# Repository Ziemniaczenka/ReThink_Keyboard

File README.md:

### Adapting older ThinkPad laptop keyboard modules into standalone keyboards using Framework Control Board.

## Hardware overview
- **Framework Control Board** - nRF54LM20A, Bluetooth/dongle/USB-C connection, nPM1300 power management IC.
- **ReThink Adapter Board** - bridge between Control Board and ThinkPad keyboards.
- **3D Printed case** - housing for components, different for each keyboard type.
- **ThinkPad keyboard modules** - 6 and 7row, classic and chiclet, with or without backlight, with integrated Pointing Stick (nub) and mouse keys. Full list TBD.
- **ZMK Firmware** - based on Zephyr RTOS, provides customizability. Each keyboard type will be different shield. See [rethink-zmk-config](https://github.com/Ziemniaczenka/rethink-zmk-config).

> Note: This is preliminary information. Everything is subject to change and more information will follow.

> [!IMPORTANT]
> While most of this repository is human-written, some of the text was written by AI, mostly in [Adapter bring-up](docs/adapter_bringup.md) and [Adapter v1.0 notes](docs/adapter_notes.md). Do with that information as you will.

## Status

- [x] Adapter Board:    V1.0 designed, parts arrived, first board assembled.
- [ ] Firmware:         repo configured, test configurations WIP.
- [ ] Case:             WIP for T420/T430, not yet started for others.

## Reference pinouts

- [Framework Control Board FFC connectors](docs/pinouts/framework_ffc.md)
- [Mezzanine Connector (e.g. T60/T420)](docs/pinouts/mezzanine.md)
- [FFC1 (e.g. L420)](docs/pinouts/ffc1.md)
- [FFC2 (e.g. T480/T580/L14)](docs/pinouts/ffc2.md)
- [PCAL6416A IO expander](docs/pinouts/io_expander.md) - expander pins, solder jumpers

## Mechanical CAD

- TBD

First case prototype (T420), 3D printed:

##  

Adapter board connects to Control Board using FFC cables, has connectors for different generations of ThinkPad keyboards, boost converters (for pointing stick, backlight) and I2C IO expander (required to keep all keyboard buttons and diodes functional).

Variants:
| Variant        | Connectors       | Backlight |
| -------------- | ---------------- | :-------: |
| Full (Default) | Mezz, FFC1, FFC2 |     ✅     |
| Mezz_no_BL     | Mezz             |     ❌     |
| FFC1           | FFC1             |     ❌     |
| FFC2           | FFC2             |     ✅     |

Solder jumpers change the defaults if needed:
- Pointing Stick supply 5V or 3V3, separately for Mezzanine/FFC1 and FFC2 (with level shifter bypass).
- IO expander supply: always on LED_3V3 (default) or switched TP_3V3.
- Charge pump and backlight boost always on, instead of controlled by the IO expander.
- 5V for T430 backlight on the Mezzanine connector (JP3, **only** for T430-like keyboards).

Defaults, jumper positions and the matching firmware options are in [IO expander](docs/pinouts/io_expander.md).

- [Schematic](circuit/ReThink_adapter_Schematic.pdf)
- [PCB](circuit/ReThink_adapter_PCB.pdf)
- [BOM](circuit/ReThink_adapter/bom/ReThink_adapter_default.csv)
- [Adapter bring-up](docs/adapter_bringup.md).
- [Adapter v1.0 notes](docs/adapter_notes.md): measurements, troubleshooting, next revision.

## Battery

- Picoblade 3-pin with NTC thermistor.
- TBD

## Firmware and Bootloader

- ZMK configuration: [rethink-zmk-config](https://github.com/Ziemniaczenka/rethink-zmk-config) (MIT), work in progress.
- Builds in Docker, the same way locally and on GitHub Actions. No Zephyr SDK needed on the PC.
- Control Board comes with MCUboot, so no programmer is needed. Flashing over USB:
  - hold the pairing button while plugging in USB,
  - or, with battery connected, hold the pairing button for 10s.
- Adapter jumpers and Control Board options (e.g. backlight power source) are set in one file: `config/rethink.conf`.

## Compatibility Table

Planned, nothing tested on real keyboards yet.

| Keyboards                                                                                               | Connector | Backlight <br> (optional) | Pointing Stick supply <br> (**default**) | Board support | Firmware config | Case |
| ------------------------------------------------------------------------------------------------------- | --------- | ------------------------- | ---------------------------------------- | ------------- | --------------- | ---- |
| T60, T61, T400, R60, R61, R400, R500, W500, W700                                                        | Mezzanine | ❌                         | 5V                                       |               |                 |      |
| T410, T420, T510, T520, W510, W520, X220                                                                | Mezzanine | ❌                         | 5V                                       | ✅             | WIP             | WIP  |
| T430, T530, W530, X230                                                                                  | Mezzanine | ✅                         | 5V                                       |               |                 |      |
| L410, L412, L420, L421, L510, L512,<br>L520, SL300, SL410, SL510                                        | FFC1      | ❌                         | 5V                                       | ✅             | WIP             |      |
| T470, T480, A475, A485                                                                                  | FFC2      | ✅                         | 3V3                                      |               |                 |      |
| T570, T580, P51s, P52s                                                                                  | FFC2      | ✅                         | 3V3                                      |               |                 |      |
| L14g1, L14g2                                                                                            | FFC2      | ✅                         | 3V3                                      |               |                 |      |
| L15g1, L15g2                                                                                            | FFC2      | ✅                         | 3V3                                      |               |                 |      |
| E480, E485, E490, E495, L380, L390, L480, L490, T480s,<br>T490, T14g1, T14g2, P43, P43s, P14sG1, P14sG2 | FFC2      | ✅                         | 3V3                                      |               |                 |      |
| E580, E585, E590, E595, L580, L590,<br>T590, P52, P53, P53s, P72, P73                                   | FFC2      | ✅                         | 3V3                                      |               |                 |      |
| T15g1, T15g2, P15sG1, P15sG2                                                                            | FFC2      | ✅                         | 3V3                                      |               |                 |      |
| P15g1, P15g2, P17g1, P17g2                                                                              | FFC2      | ✅                         | 3V3                                      |               |                 |      |

Full lists in the connector pinouts.

## License

ReThink keyboard by Ziemniaczenka is licensed under CC BY-SA 4.0.
To view a copy of this license, visit https://creativecommons.org/licenses/by-sa/4.0/

Firmware ([rethink-zmk-config](https://github.com/Ziemniaczenka/rethink-zmk-config)) is licensed under MIT.

Component 3D models located under `circuit/libraries/3dmodels/` are the intellectual property of their respective manufacturers and are provided for reference/visualization purposes only. They are not covered by the above license; all rights remain with their original owners.

## Disclaimers
> Framework Control Board was provided pre-release by Framework Computer Inc. through Control Board Developer Program.

> ThinkPad and TrackPoint are registered trademarks of Lenovo. ReThink is an independent open-source project and is not affiliated with, endorsed by, or certified by Lenovo Group Limited.

## References
1. https://github.com/FrameworkComputer/Framework-Wireless-Touchpad-Keyboard
2. https://github.com/badjeff/kb_zmk_ps2_mouse_trackpoint_driver
3. https://github.com/rampadc/zmk-thinkpad
4. https://github.com/delingren/thinkpad_keyboards
5. https://github.com/Shaedil/zmk-config-fw-cb
6. https://github.com/zmkfirmware/zmk/pull/3387

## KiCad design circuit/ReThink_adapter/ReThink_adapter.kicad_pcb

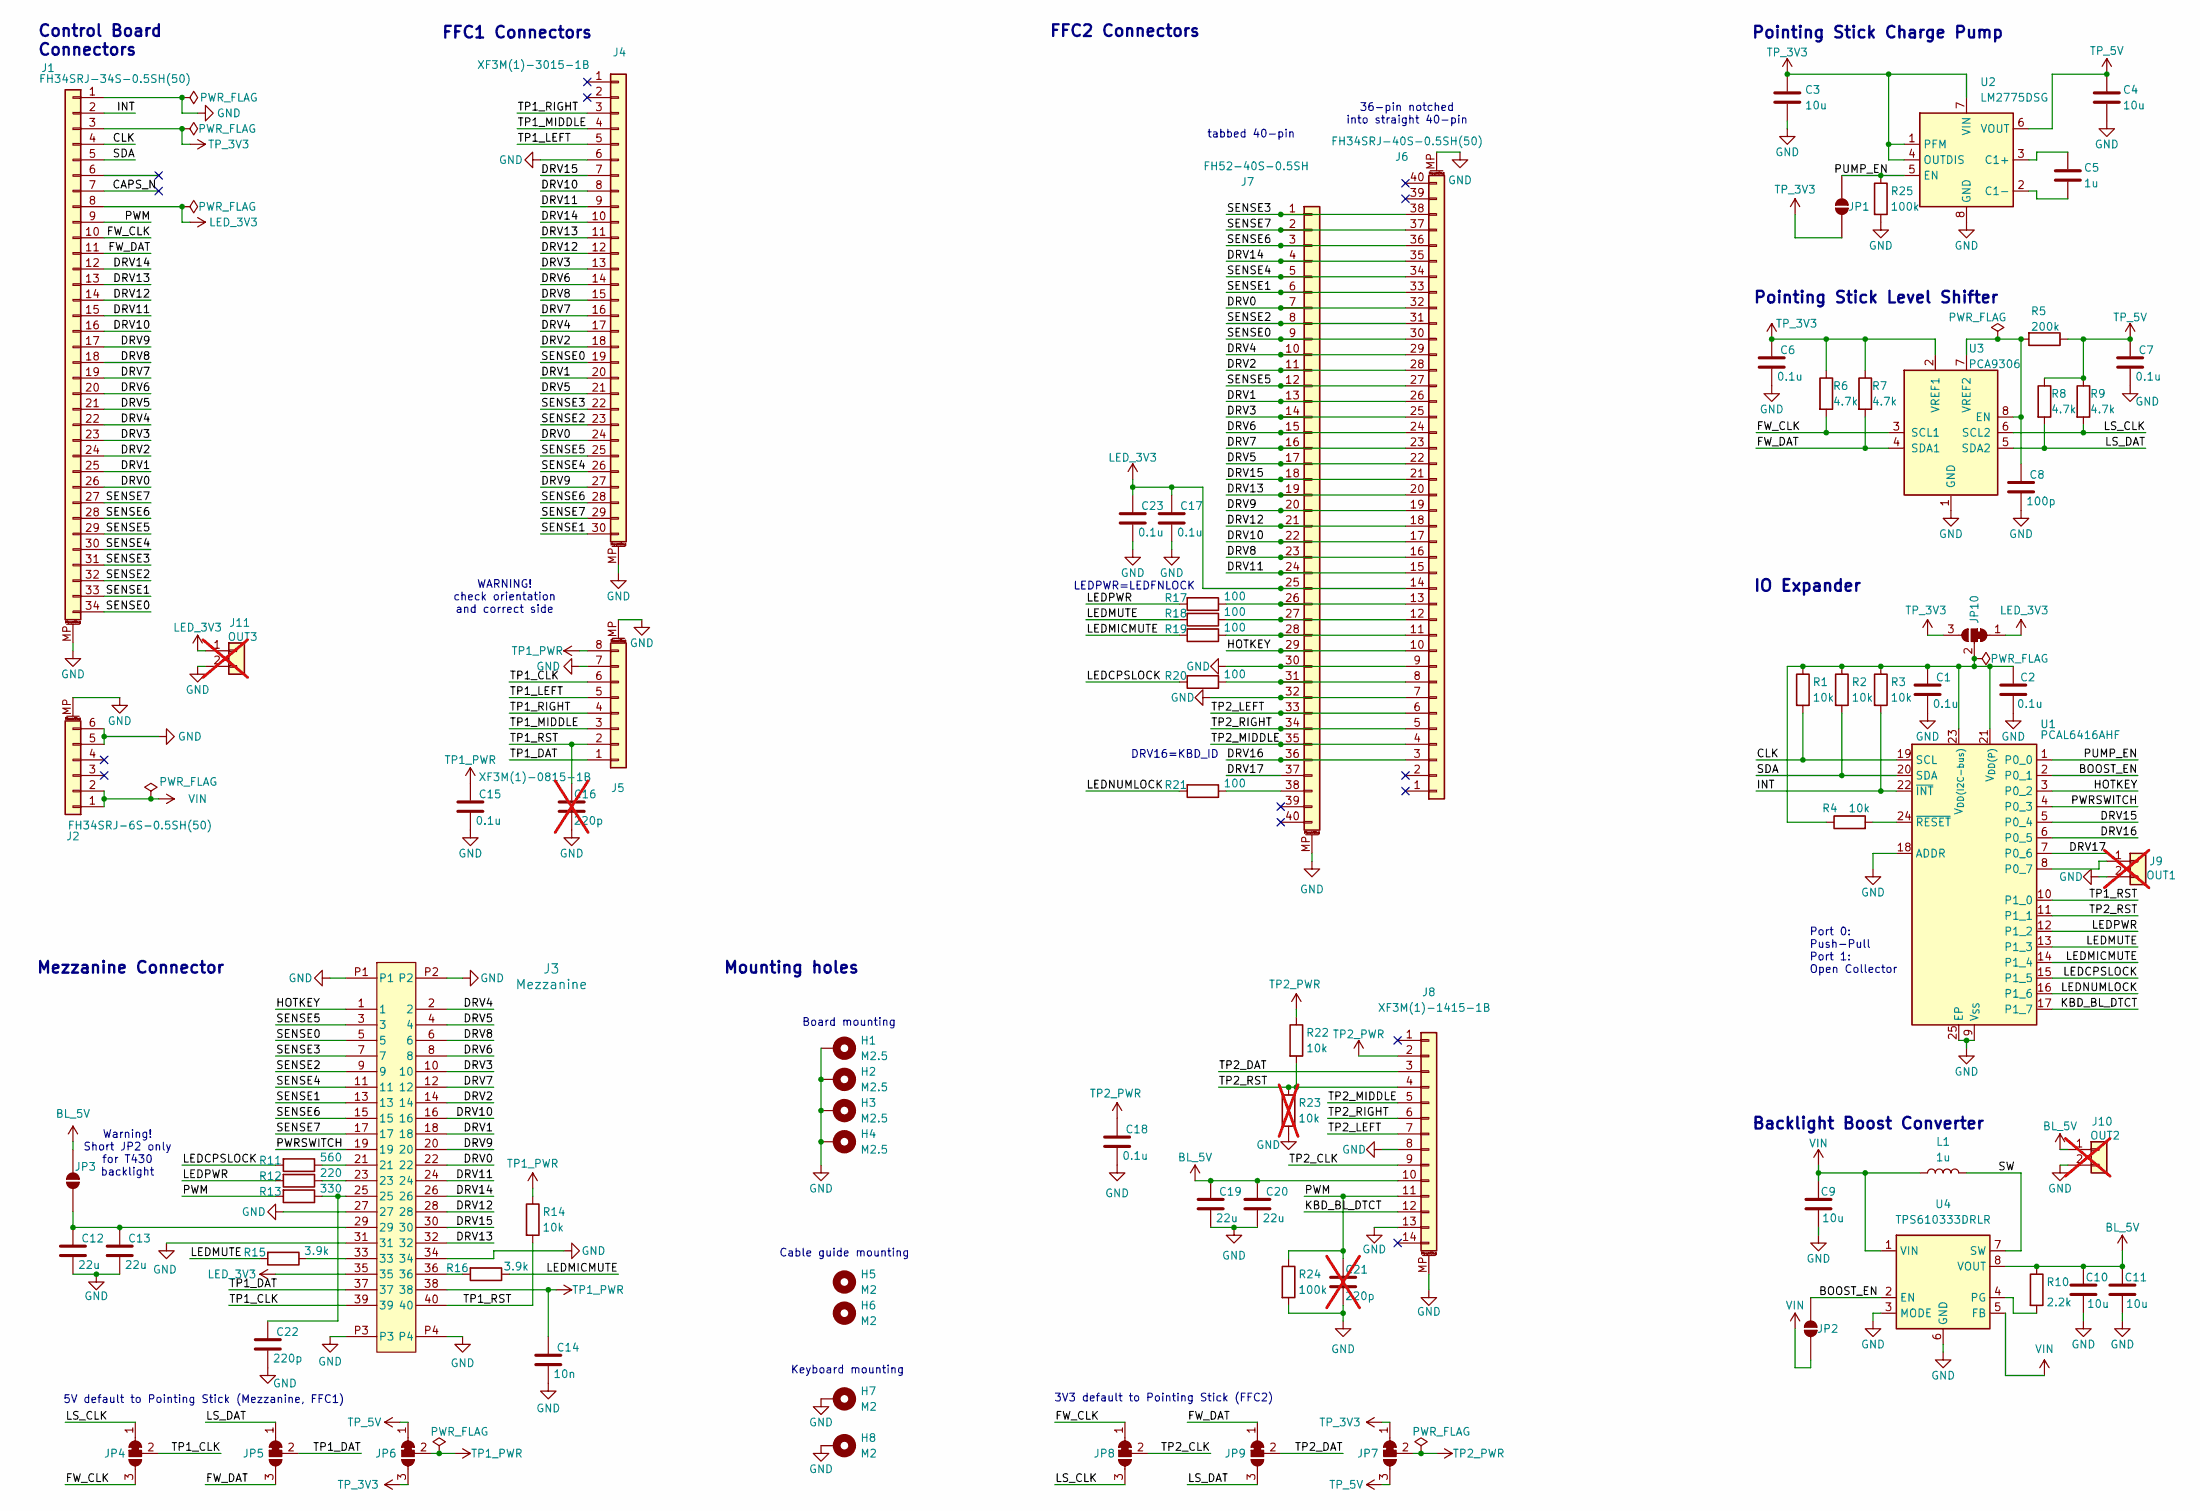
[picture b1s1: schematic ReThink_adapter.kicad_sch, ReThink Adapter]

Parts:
C1, C2, C6, C7, C15, C17, C18, C23: 0.1u; C_0402_1005Metric; Voltage 16; MPN GRM155R71H104KE14D; DigiKey_PN 490-10700-1-ND
C3, C4, C9, C10, C11: 10u; C_0603_1608Metric; Voltage 16; MPN GRM188R61E106MA73J; DigiKey_PN 1276-1869-1-ND
C5: 1u; C_0603_1608Metric; Voltage 10; MPN MLAST168SB7105KTNA01; DigiKey_PN 587-MLAST168SB7105KTNA01CT-ND
C8: 100p; C_0402_1005Metric; Voltage 25; MPN GRM1555C2A101GA01D; DigiKey_PN 490-GRM1555C2A101GA01DCT-ND
C12, C13, C19, C20: 22u; C_0805_2012Metric; Voltage 16; MPN GRM219R61C226ME15K; DigiKey_PN 490-GRM219R61C226ME15KCT-ND
C14: 10n; C_0402_1005Metric; Voltage 25; MPN CL05B103KB5NNNC; DigiKey_PN 1276-1028-1-ND
C16, C21: 220p; C_0402_1005Metric; Voltage 25; MPN C0402C221J2GACTU; DigiKey_PN 399-C0402C221J2GACTUCT-ND; not fitted
C22: 220p; C_0402_1005Metric; Voltage 25; MPN C0402C221J2GACTU; DigiKey_PN 399-C0402C221J2GACTUCT-ND
H1, H2, H3, H4: M2.5; MountingHole_2.7mm_M2.5_DIN965_Pad
H5, H6: M2; MountingHole_2.2mm_M2_ISO14580
H7, H8: M2; MountingHole_2.2mm_M2_ISO14580_Pad
J1: FH34SRJ-34S-0.5SH(50); MPN FH34SRJ-34S-0.5SH(50); DigiKey_PN 26-FH34SRJ-34S-0.5SH(50)CT-ND
J2: FH34SRJ-6S-0.5SH(50); MPN FH34SRJ-6S-0.5SH(50); DigiKey_PN H125773CT-ND
J3: Mezzanine; Mezzanine_combo; MPN AA01B-S040VA1; DigiKey_PN WM6787CT-ND
J4: XF3M(1)-3015-1B; MPN XF3M(1)-3015-1B; DigiKey_PN OR1179CT-ND
J5: XF3M(1)-0815-1B; MPN XF3M(1)-0815-1B; DigiKey_PN OR1222CT-ND
J6: FH34SRJ-40S-0.5SH(50); MPN FH34SRJ-40S-0.5SH(50); DigiKey_PN H125755CT-ND
J7: FH52-40S-0.5SH; MPN FH52-40S-0.5SH; DigiKey_PN HFZ040CT-ND
J8: XF3M(1)-1415-1B; MPN XF3M(1)-1415-1B; DigiKey_PN Z5875CT-ND
J9: OUT1; PinHeader_1x02_P2.54mm_Vertical; not fitted
J10: OUT2; PinHeader_1x02_P2.54mm_Vertical; not fitted
J11: OUT3; PinHeader_1x02_P2.54mm_Vertical; not fitted
JP1, JP2, JP3: SolderJumper_2_Open; SolderJumper-2_P1.3mm_Open_RoundedPad1.0x1.5mm
JP4, JP5, JP6, JP7, JP8, JP9, JP10: SolderJumper_3_Bridged12; SolderJumper-3_P1.3mm_Bridged12_RoundedPad1.0x1.5mm_NumberL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
L1: 1u; L_0806_2016Metric; MPN IHHP0806ZHER1R0M01; DigiKey_PN 541-IHHP0806ZHER1R0M01CT-ND
R1, R2, R3, R4, R14, R22: 10k; R_0402_1005Metric; MPN RC0402FR-0710KP; DigiKey_PN YAG1249CT-ND
R5: 200k; R_0402_1005Metric; MPN RC0402FR-07200KP; DigiKey_PN 13-RC0402FR-07200KPCT-ND
R6, R7, R8, R9: 4.7k; R_0402_1005Metric; MPN RC0402FR-074K7P; DigiKey_PN YAG1272CT-ND
R10: 2.2k; R_0402_1005Metric; MPN RC0402FR-072K2P; DigiKey_PN YAG1260CT-ND
R11: 560; R_0402_1005Metric; MPN RC0402FR-07560RL; DigiKey_PN 311-560LRCT-ND
R12: 220; R_0402_1005Metric; MPN RC0402FR-07220RP; DigiKey_PN 13-RC0402FR-07220RPCT-ND
R13: 330; R_0402_1005Metric; MPN RC0402FR-07330RL; DigiKey_PN 311-330LRCT-ND
R15, R16: 3.9k; R_0402_1005Metric; MPN RC0402FR-073K9L; DigiKey_PN 311-3.90KLRCT-ND
R17, R18, R19, R20, R21: 100; R_0402_1005Metric; MPN RC0402FR-07100RP; DigiKey_PN YAG1248CT-ND
R23: 10k; R_0402_1005Metric; MPN RC0402FR-0710KP; DigiKey_PN YAG1249CT-ND; not fitted
R24, R25: 100k; R_0402_1005Metric; MPN RC0402FR-07100KP; DigiKey_PN 13-RC0402FR-07100KPCT-ND
U1: PCAL6416AHF; HVQFN-24-1EP_4x4mm_P0.5mm_EP2.1x2.1mm; MPN PCAL6416AHF,128; DigiKey_PN 568-9946-1-ND
U2: LM2775DSG; Texas_DSG0008A_WSON-8-1EP_2x2mm_P0.5mm_EP0.9x1.6mm; MPN LM2775DSGT; DigiKey_PN 296-42149-1-ND
U3: PCA9306; VSSOP-8_2.3x2mm_P0.5mm; MPN PCA9306DCUR; DigiKey_PN 296-17988-1-ND
U4: TPS610333DRLR; SOT-583-8; MPN TPS610333DRLR; DigiKey_PN 296-TPS610333DRLRCT-ND

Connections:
/BOOST_EN: JP2.2 (B), U1.2 (P0_1), U4.2 (EN)
/CAPS_N: J1.7
/CLK: J1.4, R1.2, U1.19 (SCL)
/DRV0: J1.26, J3.22, J4.24, J6.32, J7.7
/DRV1: J1.25, J3.18, J4.20, J6.26, J7.13
/DRV2: J1.24, J3.14, J4.18, J6.28, J7.11
/DRV3: J1.23, J3.10, J4.13, J6.25, J7.14
/DRV4: J1.22, J3.2, J4.17, J6.29, J7.10
/DRV5: J1.21, J3.4, J4.21, J6.22, J7.17
/DRV6: J1.20, J3.8, J4.14, J6.24, J7.15
/DRV7: J1.19, J3.12, J4.16, J6.23, J7.16
/DRV8: J1.18, J3.6, J4.15, J6.16, J7.23
/DRV9: J1.17, J3.20, J4.27, J6.19, J7.20
/DRV10: J1.16, J3.16, J4.8, J6.17, J7.22
/DRV11: J1.15, J3.24, J4.9, J6.15, J7.24
/DRV12: J1.14, J3.28, J4.12, J6.18, J7.21
/DRV13: J1.13, J3.32, J4.11, J6.20, J7.19
/DRV14: J1.12, J3.26, J4.10, J6.35, J7.4
/DRV15: J3.30, J4.7, J6.21, J7.18, U1.5 (P0_4)
/DRV16: J6.3, J7.36, U1.6 (P0_5)
/DRV17: J7.37, U1.7 (P0_6)
/FW_CLK: J1.10, JP4.3 (B), JP8.1 (A), R6.2, U3.3 (SCL1)
/FW_DAT: J1.11, JP5.3 (B), JP9.1 (A), R7.2, U3.4 (SDA1)
/HOTKEY: J3.1, J6.10, J7.29, U1.3 (P0_2)
/INT: J1.2, R3.2, U1.22 (~INT)
/KBD_BL_DTCT: J8.12, U1.17 (P1_7)
/LEDCPSLOCK: R11.2, R20.2, U1.15 (P1_5)
/LEDMICMUTE: R16.1, R19.2, U1.14 (P1_4)
/LEDMUTE: R15.2, R18.2, U1.13 (P1_3)
/LEDNUMLOCK: R21.2, U1.16 (P1_6)
/LEDPWR: R12.2, R17.2, U1.12 (P1_2)
/LS_CLK: JP4.1 (A), JP8.3 (B), R9.2, U3.6 (SCL2)
/LS_DAT: JP5.1 (A), JP9.3 (B), R8.2, U3.5 (SDA2)
/PUMP_EN: JP1.2 (B), R25.1, U1.1 (P0_0), U2.5 (EN)
/PWM: C21.1, J1.9, J8.11, R13.2, R24.1
/PWRSWITCH: J3.19, U1.4 (P0_3)
/SDA: J1.5, R2.2, U1.20 (SDA)
/SENSE0: J1.34, J3.5, J4.19, J6.30, J7.9
/SENSE1: J1.33, J3.13, J4.30, J6.33, J7.6
/SENSE2: J1.32, J3.9, J4.23, J6.31, J7.8
/SENSE3: J1.31, J3.7, J4.22, J6.38, J7.1
/SENSE4: J1.30, J3.11, J4.26, J6.34, J7.5
/SENSE5: J1.29, J3.3, J4.25, J6.27, J7.12
/SENSE6: J1.28, J3.15, J4.28, J6.36, J7.3
/SENSE7: J1.27, J3.17, J4.29, J6.37, J7.2
/SW: L1.2, U4.7 (SW)
/TP1_CLK: J3.39, J5.6, JP4.2 (C)
/TP1_DAT: J3.37, J5.1, JP5.2 (C)
/TP1_LEFT: J4.5, J5.5
/TP1_MIDDLE: J4.4, J5.3
/TP1_RIGHT: J4.3, J5.4
/TP1_RST: C16.1, J3.40, J5.2, R14.2, U1.10 (P1_0)
/TP2_CLK: J8.9, JP8.2 (C)
/TP2_DAT: J8.3, JP9.2 (C)
/TP2_LEFT: J6.6, J7.33, J8.7
/TP2_MIDDLE: J6.4, J7.35, J8.5
/TP2_RIGHT: J6.5, J7.34, J8.6
/TP2_RST: J8.4, R22.2, R23.1, U1.11 (P1_1)
BL_5V: C10.1, C11.1, C19.1, C20.1, J8.10, J10.1, JP3.1 (A), R10.1, U4.8 (VOUT)
GND: C1.2, C2.2, C3.2, C4.2, C6.2, C7.2, C8.2, C9.2, C10.2, C11.2, C12.2, C13.2, C14.2, C15.2, C16.2, C17.2, C18.2, C19.2, C20.2, C21.2, C22.2, C23.2, H1.1 (1_1), H2.1 (1_1), H3.1 (1_1), H4.1 (1_1), H7.1 (1_1), H8.1 (1_1), J1.1, J1.MP (MountPin), J2.5, J2.6, J2.MP (MountPin), J3.27, J3.31, J3.34, J3.P1, J3.P2, J3.P3, J3.P4, J4.6, J4.MP (MountPin), J5.7, J5.MP (MountPin), J6.7, J6.9, J6.MP (MountPin), J7.30, J7.32, J7.MP (MountPin), J8.8, J8.13, J8.MP (MountPin), J9.2, J10.2, J11.2, R23.2, R24.2, R25.2, U1.9 (V_{SS}), U1.18 (ADDR), U1.25 (EP), U2.8 (GND), U2.9 (GND), U3.1 (GND), U4.3 (MODE), U4.6 (GND)
LED_3V3: C17.1, C23.1, J1.8, J3.35, J6.14, J7.25, J11.1, JP10.1 (A)
unnamed: C22.1, J3.25, R13.1
unnamed: J3.21, R11.1
unnamed: J3.23, R12.1
unnamed: J3.33, R15.1
unnamed: J3.36, R16.2
unnamed: J6.8, J7.31, R20.1
unnamed: J6.11, J7.28, R19.1
unnamed: J6.12, J7.27, R18.1
unnamed: J6.13, J7.26, R17.1
unnamed: J7.38, R21.1
unnamed: J9.1, U1.8 (P0_7)
unnamed: C12.1, C13.1, J3.29, JP3.2 (B)
unnamed: C1.1, C2.1, JP10.2 (C), R1.1, R2.1, R3.1, R4.1, U1.21 (V_{DD(P)}), U1.23 (V_{DD(I2C-bus)})
unnamed: R4.2, U1.24 (~RESET)
unnamed: C5.1, U2.3 (C1+)
unnamed: C5.2, U2.2 (C1-)
unnamed: C8.1, R5.2, U3.7 (VREF2), U3.8 (EN)
unnamed: R10.2, U4.4 (PG)
TP1_PWR: C14.1, C15.1, J3.38, J5.8, JP6.2 (C), R14.1
TP2_PWR: C18.1, J8.2, JP7.2 (C), R22.1
TP_3V3: C3.1, C6.1, J1.3, JP1.1 (A), JP6.3 (B), JP7.1 (A), JP10.3 (B), R6.1, R7.1, U2.1 (PFM), U2.4 (OUTDIS), U2.7 (VIN), U3.2 (VREF1)
TP_5V: C4.1, C7.1, JP6.1 (A), JP7.3 (B), R5.1, R8.1, R9.1, U2.6 (VOUT)
VIN: C9.1, J2.1, J2.2, JP2.1 (A), L1.1, U4.1 (VIN), U4.5 (FB)

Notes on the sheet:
IO Expander
WARNING! check orientation and correct side
Pointing Stick Level Shifter
Keyboard mounting
Control Board Connectors
Pointing Stick Charge Pump
LEDPWR=LEDFNLOCK
Backlight Boost Converter
FFC2 Connectors
FFC1 Connectors
DRV16=KBD_ID
Board mounting
3V3 default to Pointing Stick (FFC2)
Mezzanine Connector
36-pin notched into straight 40-pin
Mounting holes
Warning! Short JP2 only for T430 backlight
tabbed 40-pin
5V default to Pointing Stick (Mezzanine, FFC1)
Port 0: Push-Pull Port 1: Open Collector
Cable guide mounting

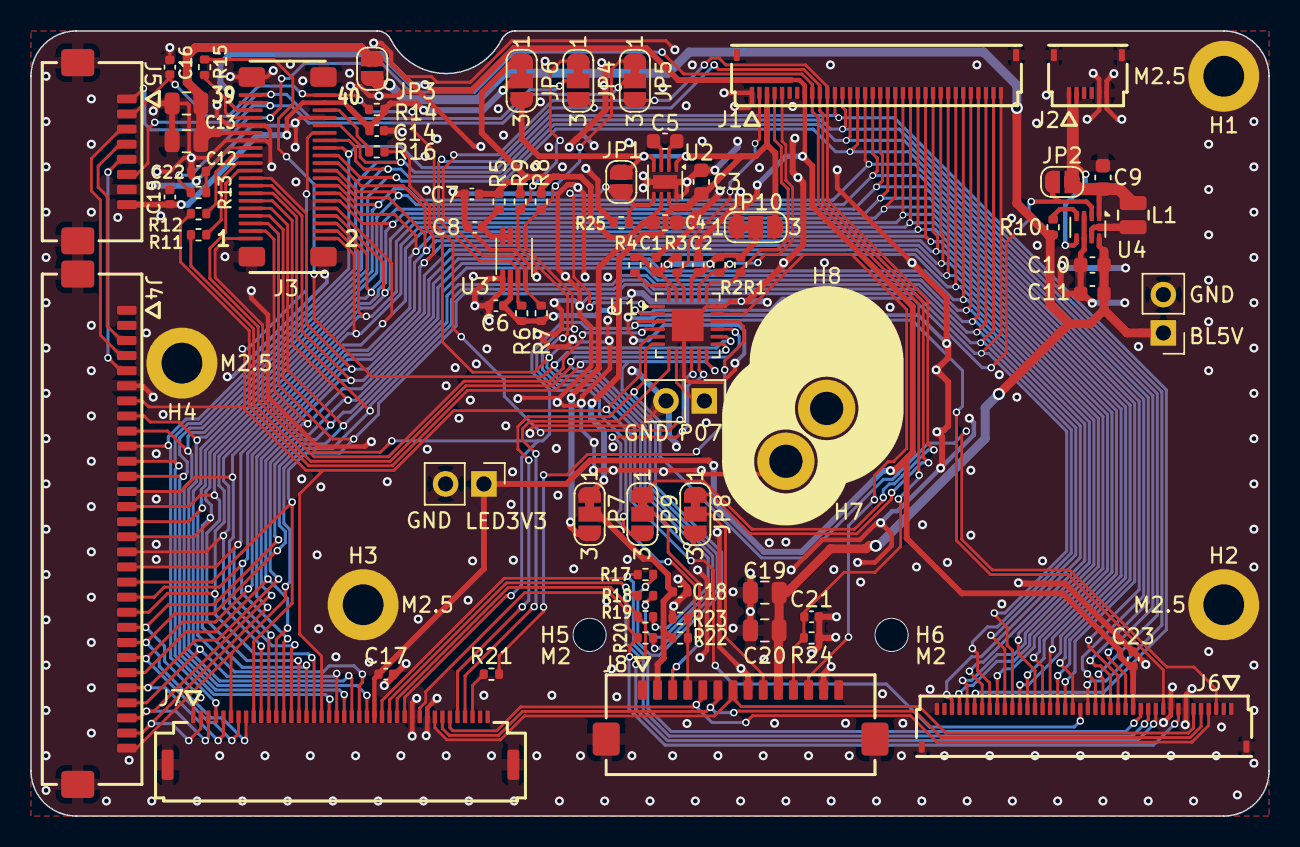
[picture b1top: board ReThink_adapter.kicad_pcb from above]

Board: 2 copper layers, 82.0 x 52.0 mm, 82 parts (0 on the bottom side), 83 nets.
